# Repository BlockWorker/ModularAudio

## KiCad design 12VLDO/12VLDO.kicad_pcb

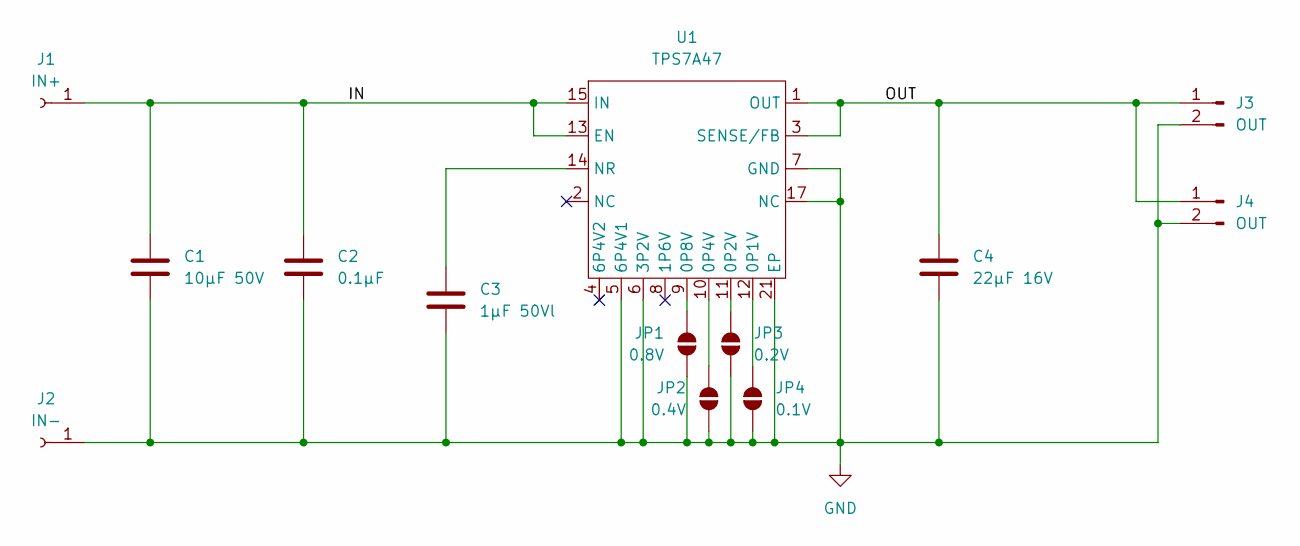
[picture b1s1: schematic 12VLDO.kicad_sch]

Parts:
C1: 10µF 50V; C_1206_3216Metric
C2: 0.1µF; C_0603_1608Metric
C3: 1µF 50Vl; C_0805_2012Metric
C4: 22µF 16V; C_1210_3225Metric
J1: IN+; SolderWirePad_1x01_SMD_1x2mm
J2: IN-; SolderWirePad_1x01_SMD_1x2mm
J3, J4: OUT; Amphenol_MINITEK_0.8_2P_V
JP1: 0.8V; SolderJumper-2_P1.3mm_Open_RoundedPad1.0x1.5mm
JP2: 0.4V; SolderJumper-2_P1.3mm_Open_RoundedPad1.0x1.5mm
JP3: 0.2V; SolderJumper-2_P1.3mm_Open_RoundedPad1.0x1.5mm
JP4: 0.1V; SolderJumper-2_P1.3mm_Open_RoundedPad1.0x1.5mm
U1: TPS7A47; Texas_RGW0020A_VQFN-20-1EP_5x5mm_P0.65mm_EP3.15x3.15mm

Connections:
/IN: C1.1, C2.1, J1.1, U1.13 (EN), U1.15 (IN), U1.16 (IN)
/OUT: C4.1, J3.1, J4.1, U1.1 (OUT), U1.3 (SENSE/FB), U1.20 (OUT)
GND: C1.2, C2.2, C3.2, C4.2, J2.1, J3.2, J4.2, JP1.1 (A), JP2.1 (A), JP3.1 (A), JP4.1 (A), U1.5 (6P4V1), U1.6 (3P2V), U1.7 (GND), U1.17 (NC), U1.18 (NC), U1.19 (NC), U1.21 (EP)
unnamed: JP1.2 (B), U1.9 (0P8V)
unnamed: JP2.2 (B), U1.10 (0P4V)
unnamed: JP3.2 (B), U1.11 (0P2V)
unnamed: JP4.2 (B), U1.12 (0P1V)
unnamed: C3.1, U1.14 (NR)

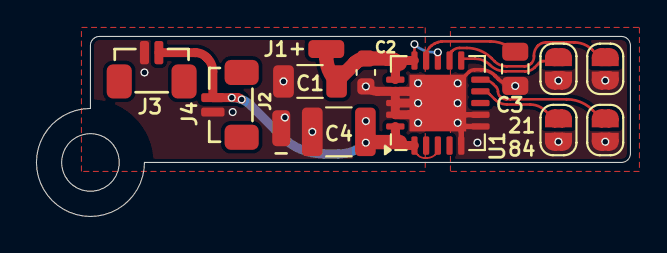
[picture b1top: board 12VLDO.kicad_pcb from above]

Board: 2 copper layers, 33.0 x 10.0 mm, 13 parts (0 on the bottom side), 8 nets.

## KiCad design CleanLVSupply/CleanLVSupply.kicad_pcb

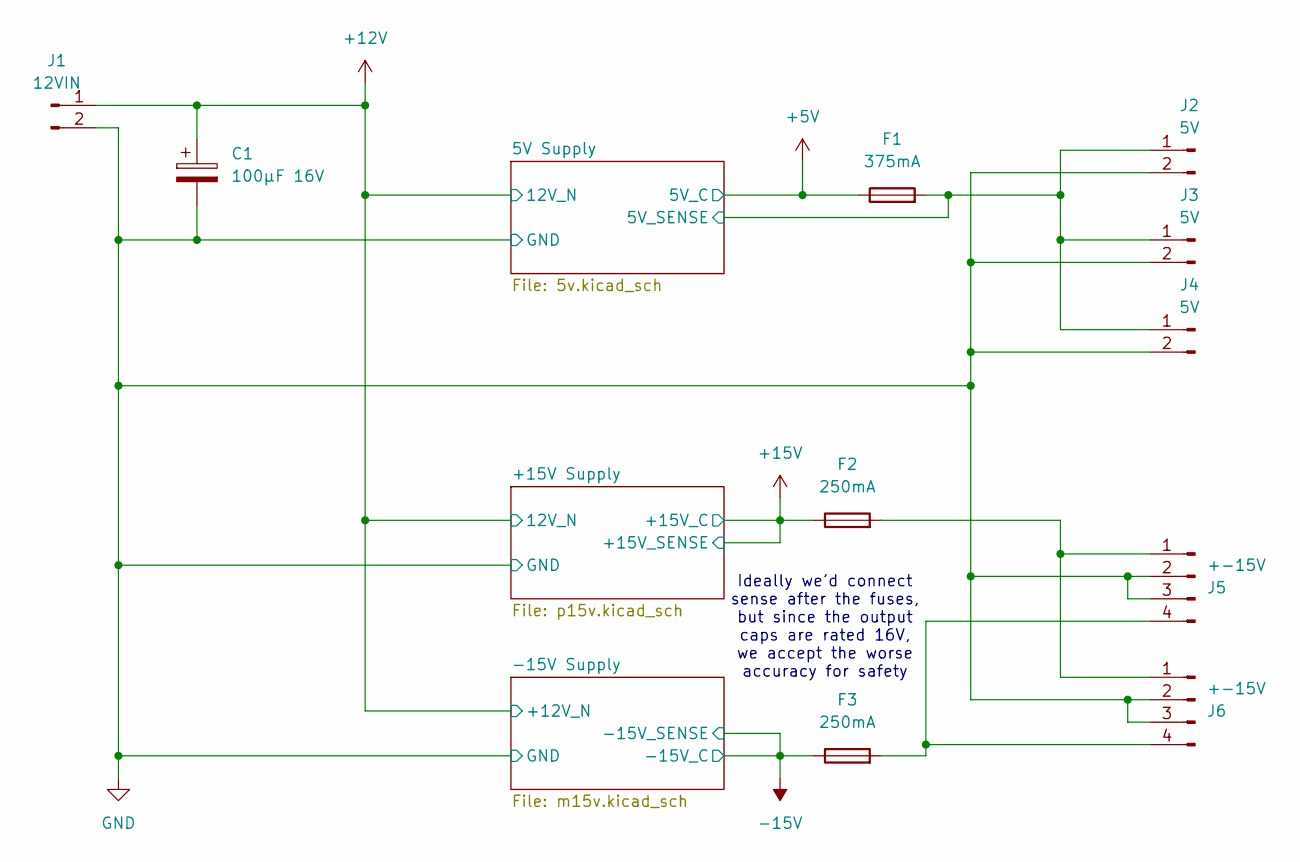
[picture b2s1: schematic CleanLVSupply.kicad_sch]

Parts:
C1: 100µF 16V; CP_Elec_6.3x5.8
F1: 375mA; Fuse_0603_1608Metric
F2, F3: 250mA; Fuse_0603_1608Metric
J1: 12VIN; Amphenol_MINITEK_0.8_2P_V
J2, J3, J4: 5V; Amphenol_MINITEK_0.8_2P_V
J5, J6: +-15V; Amphenol_MINITEK_0.8_4P_V

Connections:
+5V: F1.1; also elsewhere on the board
+12V: C1.1, J1.1; also elsewhere on the board
+15V: F2.1; also elsewhere on the board
-15V: F3.1; also elsewhere on the board
/5V Supply/5V_SENSE: F1.2, J2.1, J3.1, J4.1; also elsewhere on the board
GND: C1.2, J1.2, J2.2, J3.2, J4.2, J5.2, J5.3, J6.2, J6.3; also elsewhere on the board
unnamed: F2.2, J5.1, J6.1
unnamed: F3.2, J5.4, J6.4

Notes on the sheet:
Ideally we'd connect sense after the fuses, but since the output caps are rated 16V, we accept the worse accuracy for safety

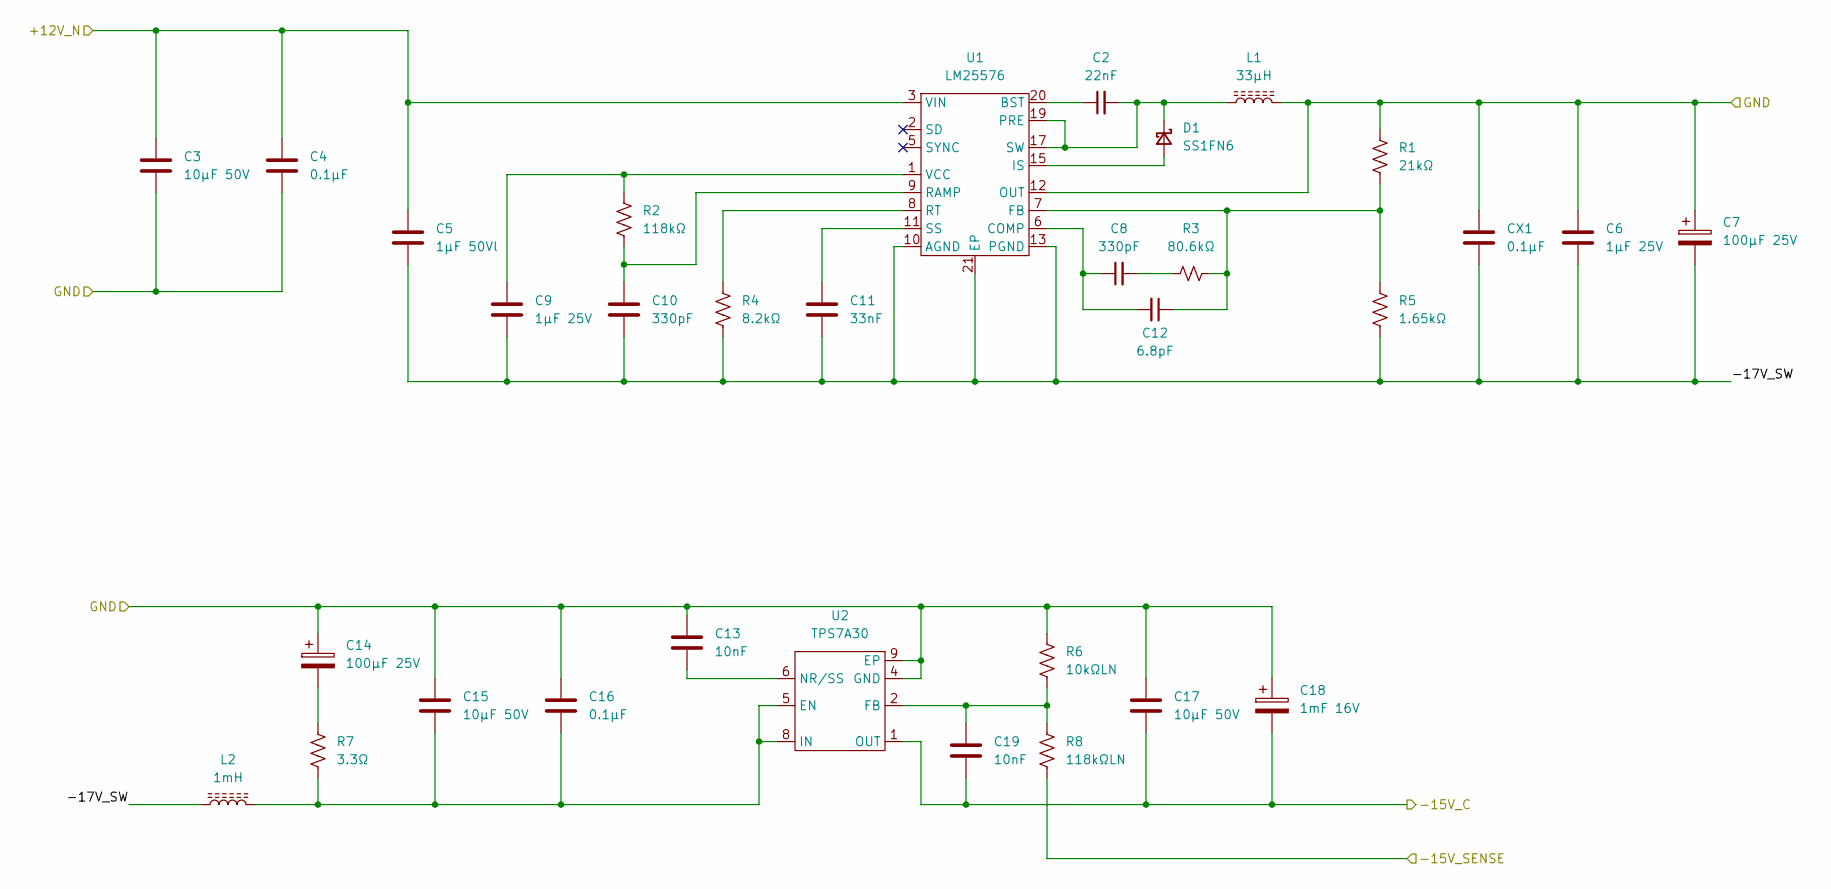
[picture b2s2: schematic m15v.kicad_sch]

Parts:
C2: 22nF; C_0603_1608Metric
C3, C15, C17: 10µF 50V; C_1206_3216Metric
C4, C16: 0.1µF; C_0603_1608Metric
C5: 1µF 50Vl; C_0805_2012Metric
C6, C9: 1µF 25V; C_0603_1608Metric
C7: 100µF 25V; CP_Elec_6.3x7.7
C8, C10: 330pF; C_0603_1608Metric
C11: 33nF; C_0603_1608Metric
C12: 6.8pF; C_0603_1608Metric
C13, C19: 10nF; C_0603_1608Metric
C14: 100µF 25V; CP_Radial_D6.3mm_P2.50mm
C18: 1mF 16V; CP_Radial_D8.0mm_P3.50mm
CX1: 0.1µF; C_0603_1608Metric
D1: SS1FN6; D_SMF
L1: 33µH; L_KEMET_MPGV1D1054
L2: 1mH; L_Coilcraft_MSS7348-XXX-fixed
R1: 21kΩ; R_0603_1608Metric
R2: 118kΩ; R_0603_1608Metric
R3: 80.6kΩ; R_0603_1608Metric
R4: 8.2kΩ; R_0603_1608Metric
R5: 1.65kΩ; R_0603_1608Metric
R6: 10kΩLN; R_0603_1608Metric
R7: 3.3Ω; R_0805_2012Metric
R8: 118kΩLN; R_0603_1608Metric
U1: LM25576; HTSSOP-20-1EP_4.4x6.5mm_P0.65mm_EP2.85x4mm
U2: TPS7A30; HVSSOP-8-1EP_3x3mm_P0.65mm_EP1.57x1.89mm

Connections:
+12V: C3.1, C4.1, C5.1, U1.3 (VIN), U1.4 (VIN); also elsewhere on the board
-15V: C17.2, C18.2, C19.2, R8.2, U2.1 (OUT); also elsewhere on the board
/-15V Supply/-17V_SW: C5.2, C6.2, C7.2, C9.2, C10.2, C11.2, CX1.2, L2.1, R4.2, R5.2, U1.10 (AGND), U1.13 (PGND), U1.14 (PGND), U1.21 (EP)
GND: C3.2, C4.2, C6.1, C7.1, C13.1, C14.1, C15.1, C16.1, C17.1, C18.1, CX1.1, L1.2, R1.1, R6.1, U1.12 (OUT), U2.4 (GND), U2.9 (EP); also elsewhere on the board
unnamed: C8.2, R3.1
unnamed: C14.2, R7.1
unnamed: D1.2 (A), U1.15 (IS), U1.16 (IS)
unnamed: C2.2, D1.1 (K), L1.1, U1.17 (SW), U1.18 (SW), U1.19 (PRE)
unnamed: C2.1, U1.20 (BST)
unnamed: C8.1, C12.2, U1.6 (COMP)
unnamed: C12.1, R1.2, R3.2, R5.1, U1.7 (FB)
unnamed: C10.1, R2.2, U1.9 (RAMP)
unnamed: R4.1, U1.8 (RT)
unnamed: C11.1, U1.11 (SS)
unnamed: C9.1, R2.1, U1.1 (VCC)
unnamed: C15.2, C16.2, L2.2, R7.2, U2.5 (EN), U2.8 (IN)
unnamed: C19.1, R6.2, R8.1, U2.2 (FB)
unnamed: C13.2, U2.6 (NR/SS)

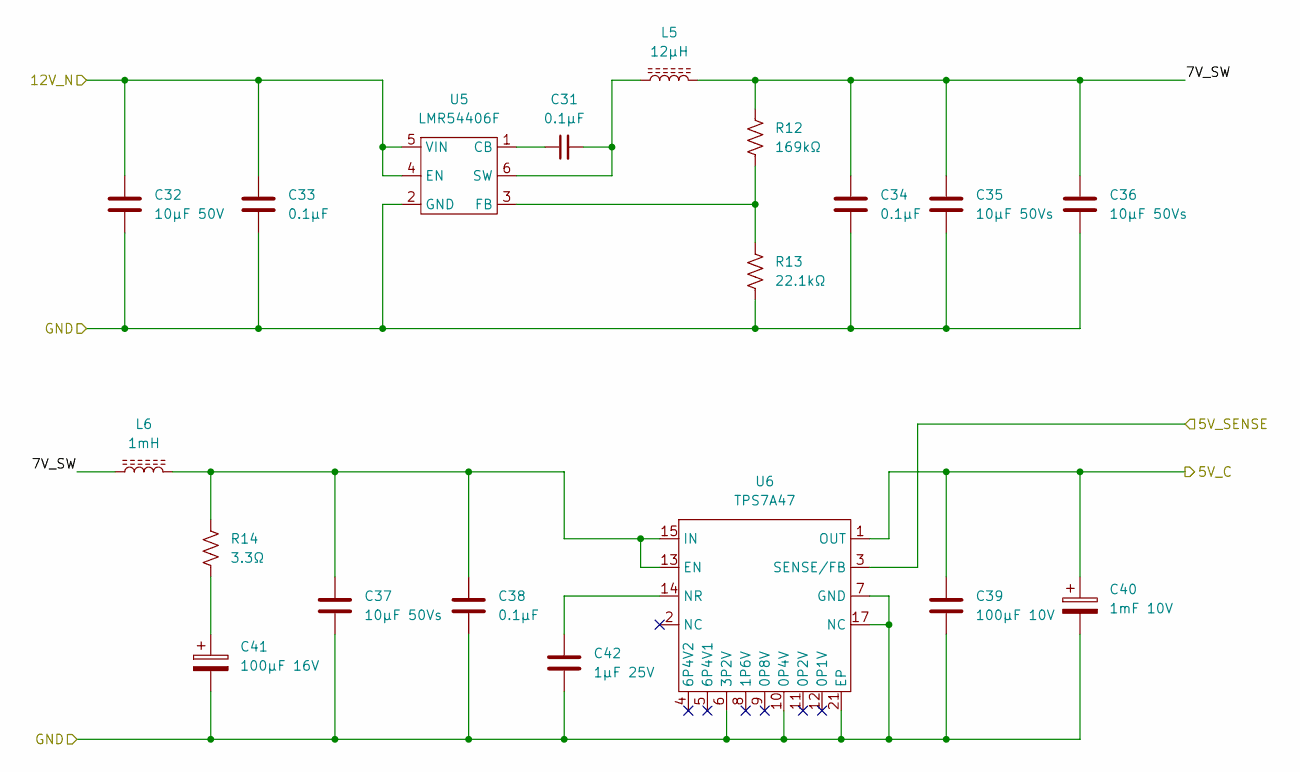
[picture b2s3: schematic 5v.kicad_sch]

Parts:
C31, C33, C34, C38: 0.1µF; C_0603_1608Metric
C32: 10µF 50V; C_1206_3216Metric
C35, C36, C37: 10µF 50Vs; C_0805_2012Metric
C39: 100µF 10V; C_1210_3225Metric
C40: 1mF 10V; CP_Radial_D8.0mm_P3.50mm
C41: 100µF 16V; CP_Radial_D5.0mm_P2.00mm
C42: 1µF 25V; C_0603_1608Metric
L5: 12µH; L_Bourns_SRR4528A
L6: 1mH; L_Coilcraft_MSS7348-XXX-fixed
R12: 169kΩ; R_0603_1608Metric
R13: 22.1kΩ; R_0603_1608Metric
R14: 3.3Ω; R_0805_2012Metric
U5: LMR54406F; SOT-23-6
U6: TPS7A47; Texas_RGW0020A_VQFN-20-1EP_5x5mm_P0.65mm_EP3.15x3.15mm

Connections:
+5V: C39.1, C40.1, U6.1 (OUT), U6.20 (OUT); also elsewhere on the board
+12V: C32.1, C33.1, U5.4 (EN), U5.5 (VIN); also elsewhere on the board
/5V Supply/5V_SENSE: U6.3 (SENSE/FB); also elsewhere on the board
/5V Supply/7V_SW: C34.1, C35.1, C36.1, L5.2, L6.1, R12.1
GND: C32.2, C33.2, C34.2, C35.2, C36.2, C37.2, C38.2, C39.2, C40.2, C41.2, C42.2, R13.2, U5.2 (GND), U6.6 (3P2V), U6.7 (GND), U6.10 (0P4V), U6.17 (NC), U6.18 (NC), U6.19 (NC), U6.21 (EP); also elsewhere on the board
unnamed: C41.1, R14.2
unnamed: C31.1, U5.1 (CB)
unnamed: R12.2, R13.1, U5.3 (FB)
unnamed: C31.2, L5.1, U5.6 (SW)
unnamed: C37.1, C38.1, L6.2, R14.1, U6.13 (EN), U6.15 (IN), U6.16 (IN)
unnamed: C42.1, U6.14 (NR)

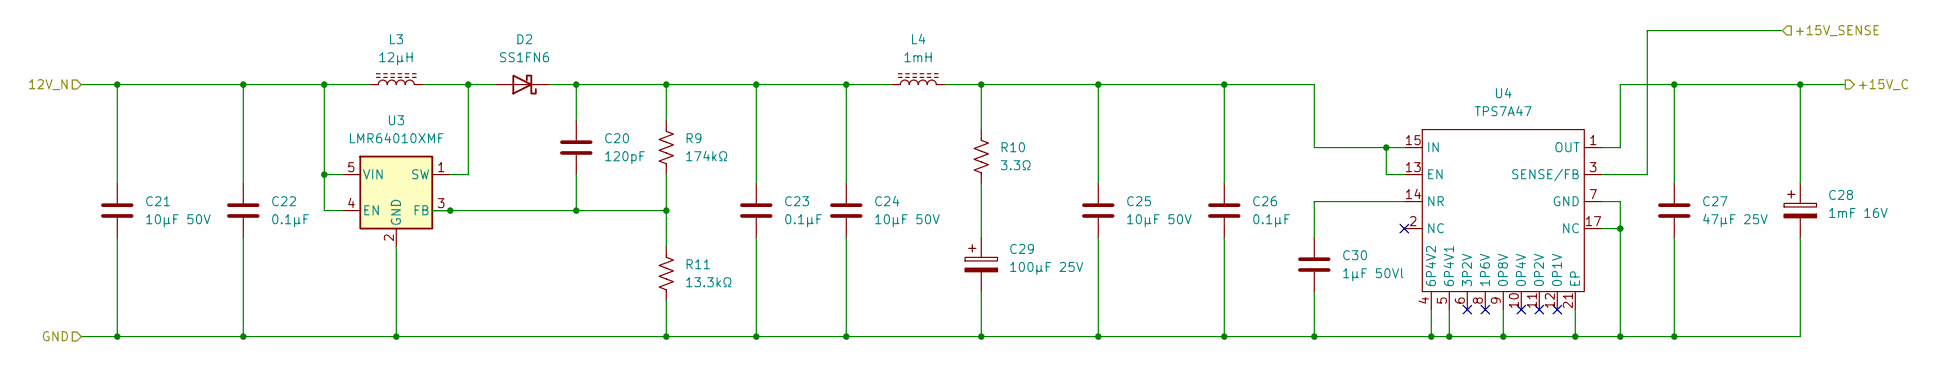
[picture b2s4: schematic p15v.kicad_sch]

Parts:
C20: 120pF; C_0603_1608Metric
C21, C24, C25: 10µF 50V; C_1206_3216Metric
C22, C23, C26: 0.1µF; C_0603_1608Metric
C27: 47µF 25V; C_2220_5750Metric
C28: 1mF 16V; CP_Radial_D8.0mm_P3.50mm
C29: 100µF 25V; CP_Radial_D6.3mm_P2.50mm
C30: 1µF 50Vl; C_0805_2012Metric
D2: SS1FN6; D_SMF
L3: 12µH; L_Abracon_ASPI-6045S
L4: 1mH; L_Coilcraft_MSS7348-XXX-fixed
R9: 174kΩ; R_0603_1608Metric
R10: 3.3Ω; R_0805_2012Metric
R11: 13.3kΩ; R_0603_1608Metric
U3: LMR64010XMF; SOT-23-5
U4: TPS7A47; Texas_RGW0020A_VQFN-20-1EP_5x5mm_P0.65mm_EP3.15x3.15mm

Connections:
+12V: C21.1, C22.1, L3.1, U3.4 (EN), U3.5 (VIN); also elsewhere on the board
+15V: C27.1, C28.1, U4.1 (OUT), U4.3 (SENSE/FB), U4.20 (OUT); also elsewhere on the board
GND: C21.2, C22.2, C23.2, C24.2, C25.2, C26.2, C27.2, C28.2, C29.2, C30.2, R11.2, U3.2 (GND), U4.4 (6P4V2), U4.5 (6P4V1), U4.7 (GND), U4.9 (0P8V), U4.17 (NC), U4.18 (NC), U4.19 (NC), U4.21 (EP); also elsewhere on the board
unnamed: C29.1, R10.2
unnamed: D2.2 (A), L3.2, U3.1 (SW)
unnamed: C20.1, C23.1, C24.1, D2.1 (K), L4.1, R9.1
unnamed: C20.2, R9.2, R11.1, U3.3 (FB)
unnamed: C25.1, C26.1, L4.2, R10.1, U4.13 (EN), U4.15 (IN), U4.16 (IN)
unnamed: C30.1, U4.14 (NR)

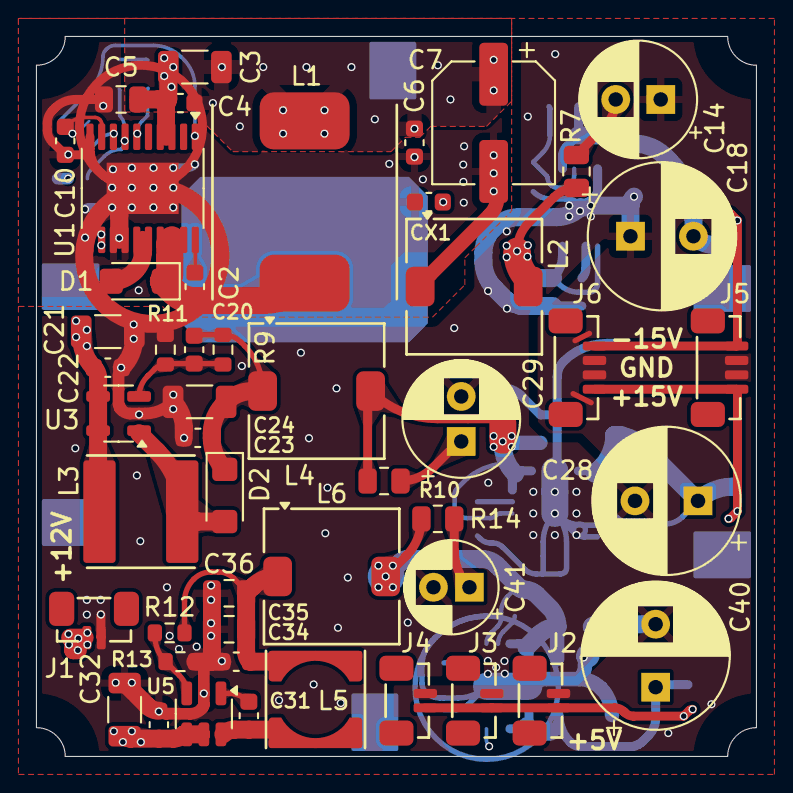
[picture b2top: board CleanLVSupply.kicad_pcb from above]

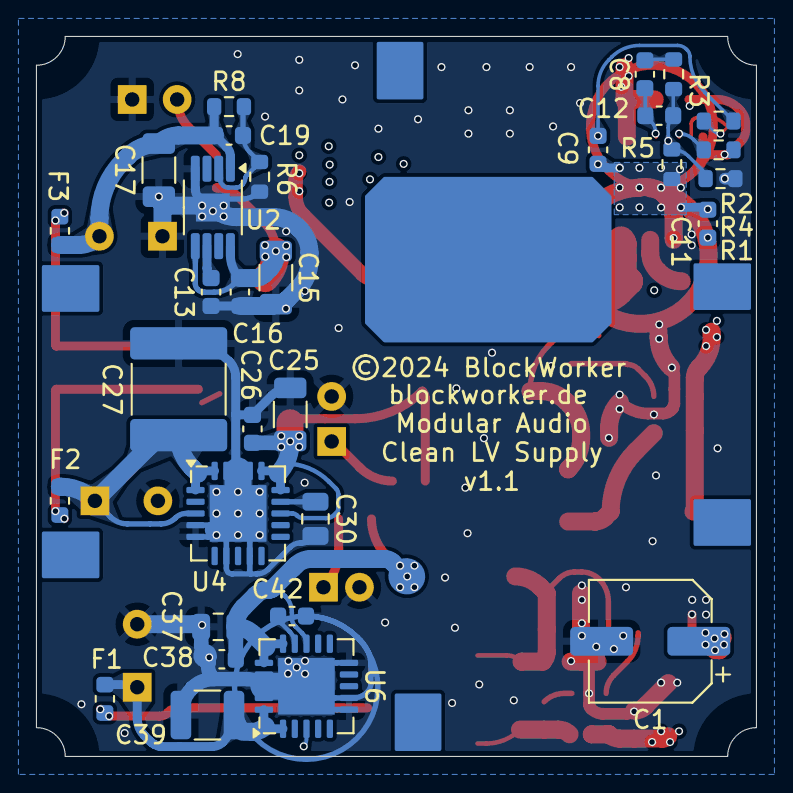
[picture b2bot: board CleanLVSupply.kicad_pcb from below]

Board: 4 copper layers, 40.0 x 40.0 mm, 80 parts (31 on the bottom side), 36 nets.

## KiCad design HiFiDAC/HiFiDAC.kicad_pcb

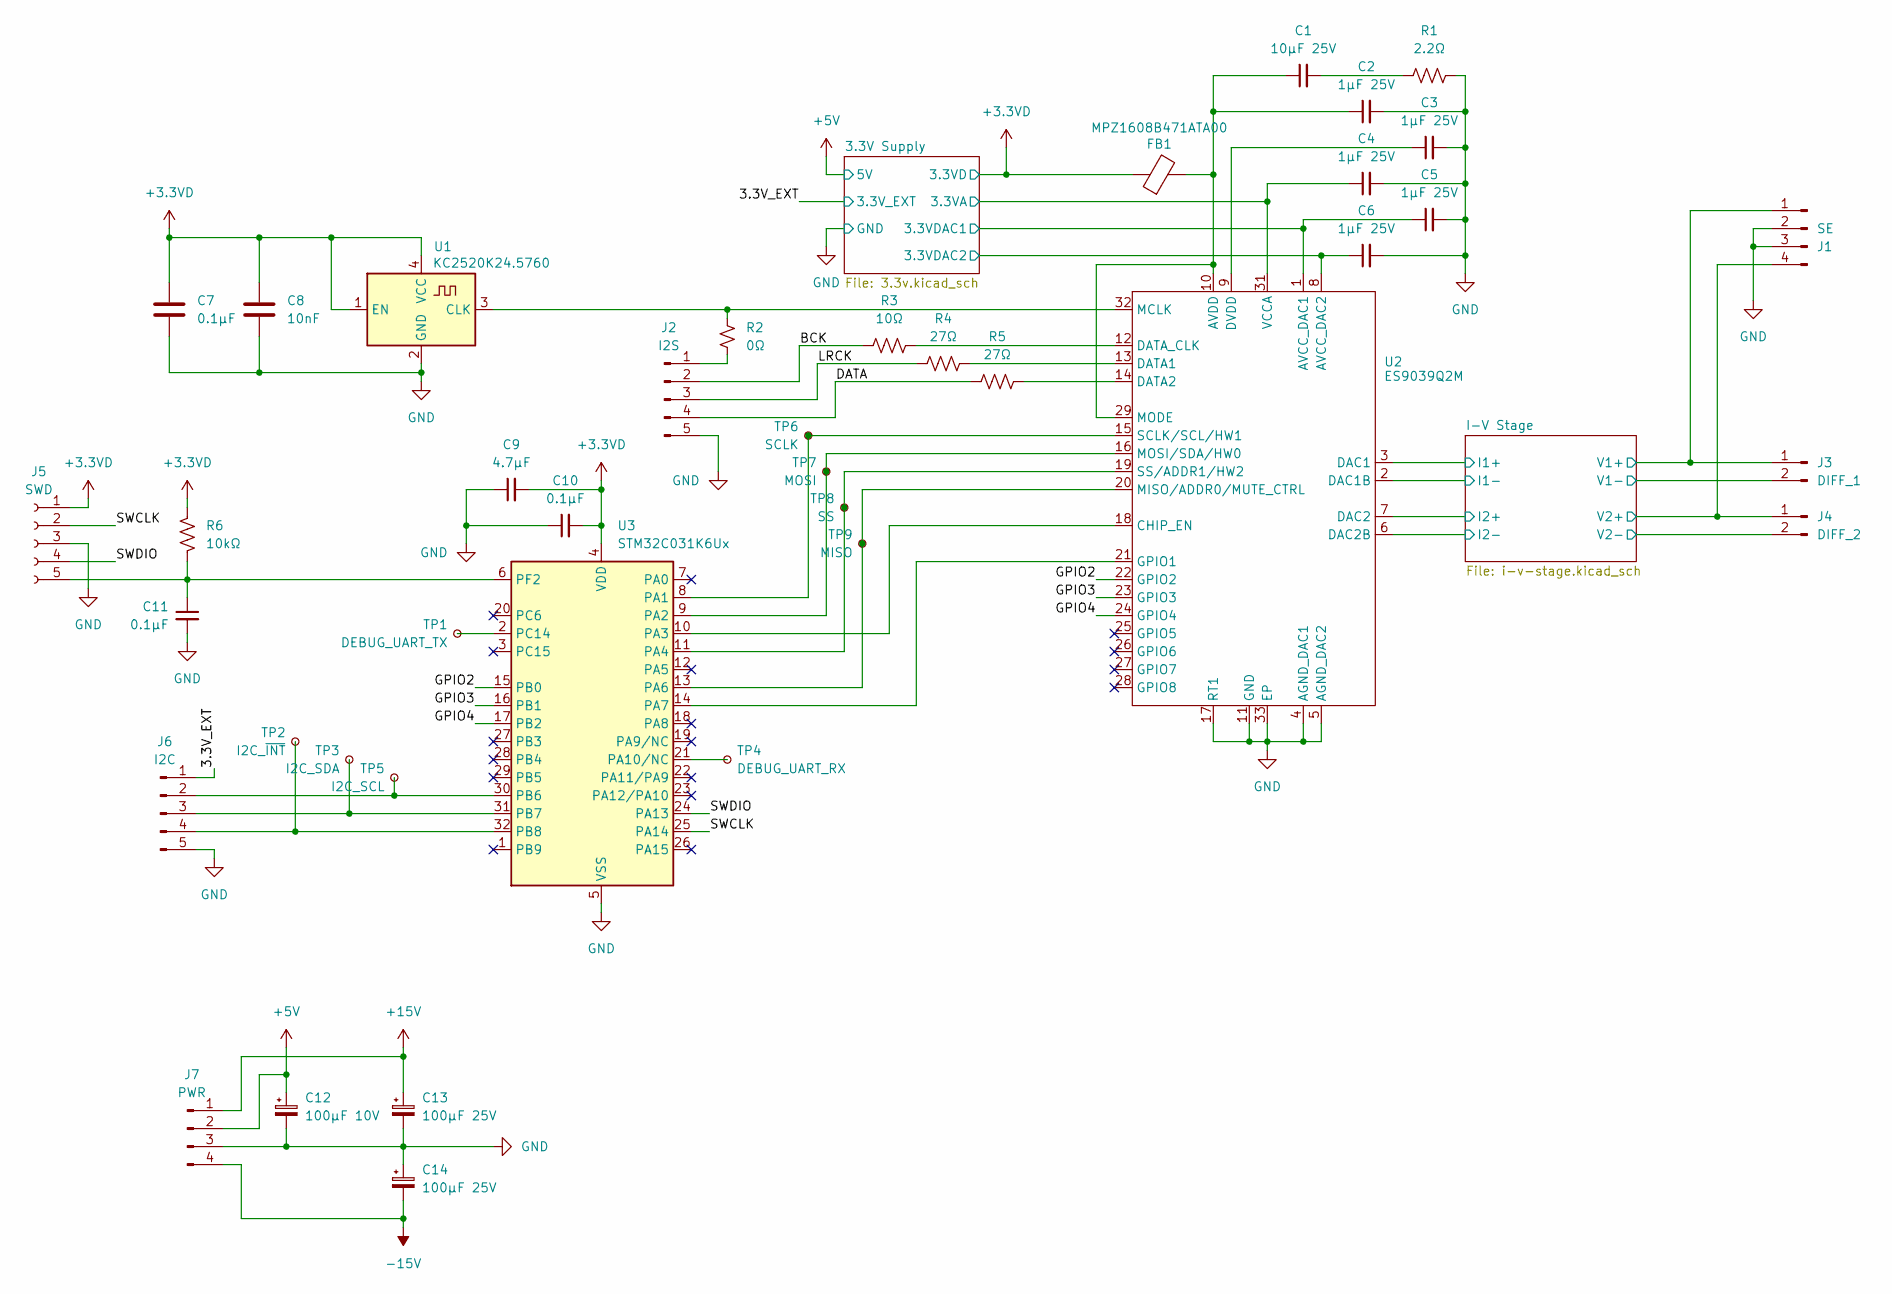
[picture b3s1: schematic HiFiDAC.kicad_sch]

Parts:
C1: 10µF 25V; C_0805_2012Metric
C2, C3, C4, C5, C6: 1µF 25V; C_0603_1608Metric
C7, C10, C11: 0.1µF; C_0603_1608Metric
C8: 10nF; C_0603_1608Metric
C9: 4.7µF; C_0603_1608Metric
C12: 100µF 10V; CP_Radial_D6.3mm_P2.50mm
C13, C14: 100µF 25V; CP_Elec_6.3x5.9
FB1: MPZ1608B471ATA00; L_0603_1608Metric
J1: SE; Amphenol_MINITEK_0.8_4P_V
J2: I2S; Amphenol_MINITEK_WTB_1.25_5P_V
J3: DIFF_1; Amphenol_MINITEK_0.8_2P_V
J4: DIFF_2; Amphenol_MINITEK_0.8_2P_V
J5: SWD; PinSocket_1x05_P1.27mm_Vertical_SMD_Pin1Right
J6: I2C; Amphenol_MINITEK_WTB_1.25_5P_V
J7: PWR; Amphenol_MINITEK_WTB_1.25_4P_V
R1: 2.2Ω; R_0603_1608Metric
R2: 0Ω; R_0603_1608Metric
R3: 10Ω; R_0603_1608Metric
R4, R5: 27Ω; R_0603_1608Metric
R6: 10kΩ; R_0603_1608Metric
TP1: DEBUG_UART_TX; TP_0603_1608Metric_Fused
TP2: I2C_~{INT}; TP_0603_1608Metric_Fused
TP3: I2C_SDA; TP_0603_1608Metric_Fused
TP4: DEBUG_UART_RX; TP_0603_1608Metric_Fused
TP5: I2C_SCL; TP_0603_1608Metric_Fused
TP6: SCLK; TP_0603_1608Metric_Fused
TP7: MOSI; TP_0603_1608Metric_Fused
TP8: SS; TP_0603_1608Metric_Fused
TP9: MISO; TP_0603_1608Metric_Fused
U1: KC2520K24.5760; Oscillator_SMD_Kyocera_KC2520Z-4Pin_2.5x2.0mm
U2: ES9039Q2M; QFN-32-1EP_5x5mm_P0.5mm_EP3.2x3.2mm
U3: STM32C031K6Ux; QFN-32-1EP_5x5mm_P0.5mm_EP3.45x3.45mm

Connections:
+3.3VD: C7.1, C8.1, C9.2, C10.2, FB1.1, J5.1, R6.1, U1.1 (EN), U1.4 (VCC), U3.4 (VDD); also elsewhere on the board
+5V: C12.1, J7.2; also elsewhere on the board
+15V: C13.1, J7.1; also elsewhere on the board
-15V: C14.2, J7.4; also elsewhere on the board
/3.3V Supply/3.3VA: C4.1, U2.31 (VCCA); also elsewhere on the board
/3.3V Supply/3.3VDAC1: C5.1, U2.1 (AVCC_DAC1); also elsewhere on the board
/3.3V Supply/3.3VDAC2: C6.1, U2.8 (AVCC_DAC2); also elsewhere on the board
/3.3V_EXT: J6.1; also elsewhere on the board
/BCK: J2.2, R3.1
/DATA: J2.4, R5.1
/GPIO2: U2.22 (GPIO2), U3.15 (PB0)
/GPIO3: U2.23 (GPIO3), U3.16 (PB1)
/GPIO4: U2.24 (GPIO4), U3.17 (PB2)
/I-V Stage/I1+: U2.3 (DAC1); also elsewhere on the board
/I-V Stage/I1-: U2.2 (DAC1B); also elsewhere on the board
/I-V Stage/I2+: U2.7 (DAC2); also elsewhere on the board
/I-V Stage/I2-: U2.6 (DAC2B); also elsewhere on the board
/I-V Stage/V1+: J1.1, J3.1; also elsewhere on the board
/I-V Stage/V1-: J3.2; also elsewhere on the board
/I-V Stage/V2+: J1.4, J4.1; also elsewhere on the board
/I-V Stage/V2-: J4.2; also elsewhere on the board
/LRCK: J2.3, R4.1
/SWCLK: J5.2, U3.25 (PA14)
/SWDIO: J5.4, U3.24 (PA13)
GND: C2.2, C3.2, C4.2, C5.2, C6.2, C7.2, C8.2, C9.1, C10.1, C11.2, C12.2, C13.2, C14.1, J1.2, J1.3, J2.5, J5.3, J6.5, J7.3, R1.1, U1.2 (GND), U2.4 (AGND_DAC1), U2.5 (AGND_DAC2), U2.11 (GND), U2.17 (RT1), U2.30 (GND), U2.33 (EP), U3.5 (VSS), U3.33 (VSS); also elsewhere on the board
unnamed: C1.2, R1.2
unnamed: J2.1, R2.1
unnamed: C11.1, J5.5, R6.2, U3.6 (PF2)
unnamed: J6.2, TP5.1, U3.30 (PB6)
unnamed: J6.3, TP3.1, U3.31 (PB7)
unnamed: J6.4, TP2.1, U3.32 (PB8)
unnamed: R2.2, U1.3 (CLK), U2.32 (MCLK)
unnamed: C1.1, C2.1, FB1.2, U2.10 (AVDD), U2.29 (MODE)
unnamed: U2.18 (CHIP_EN), U3.10 (PA3)
unnamed: R4.2, U2.13 (DATA1)
unnamed: R5.2, U2.14 (DATA2)
unnamed: R3.2, U2.12 (DATA_CLK)
unnamed: C3.1, U2.9 (DVDD)
unnamed: U2.21 (GPIO1), U3.14 (PA7)
unnamed: TP9.1, U2.20 (MISO/ADDR0/MUTE_CTRL), U3.13 (PA6)
unnamed: TP7.1, U2.16 (MOSI/SDA/HW0), U3.9 (PA2)
unnamed: TP6.1, U2.15 (SCLK/SCL/HW1), U3.8 (PA1)
unnamed: TP8.1, U2.19 (SS/ADDR1/HW2), U3.11 (PA4)
unnamed: TP4.1, U3.21 (PA10/NC)
unnamed: TP1.1, U3.2 (PC14)

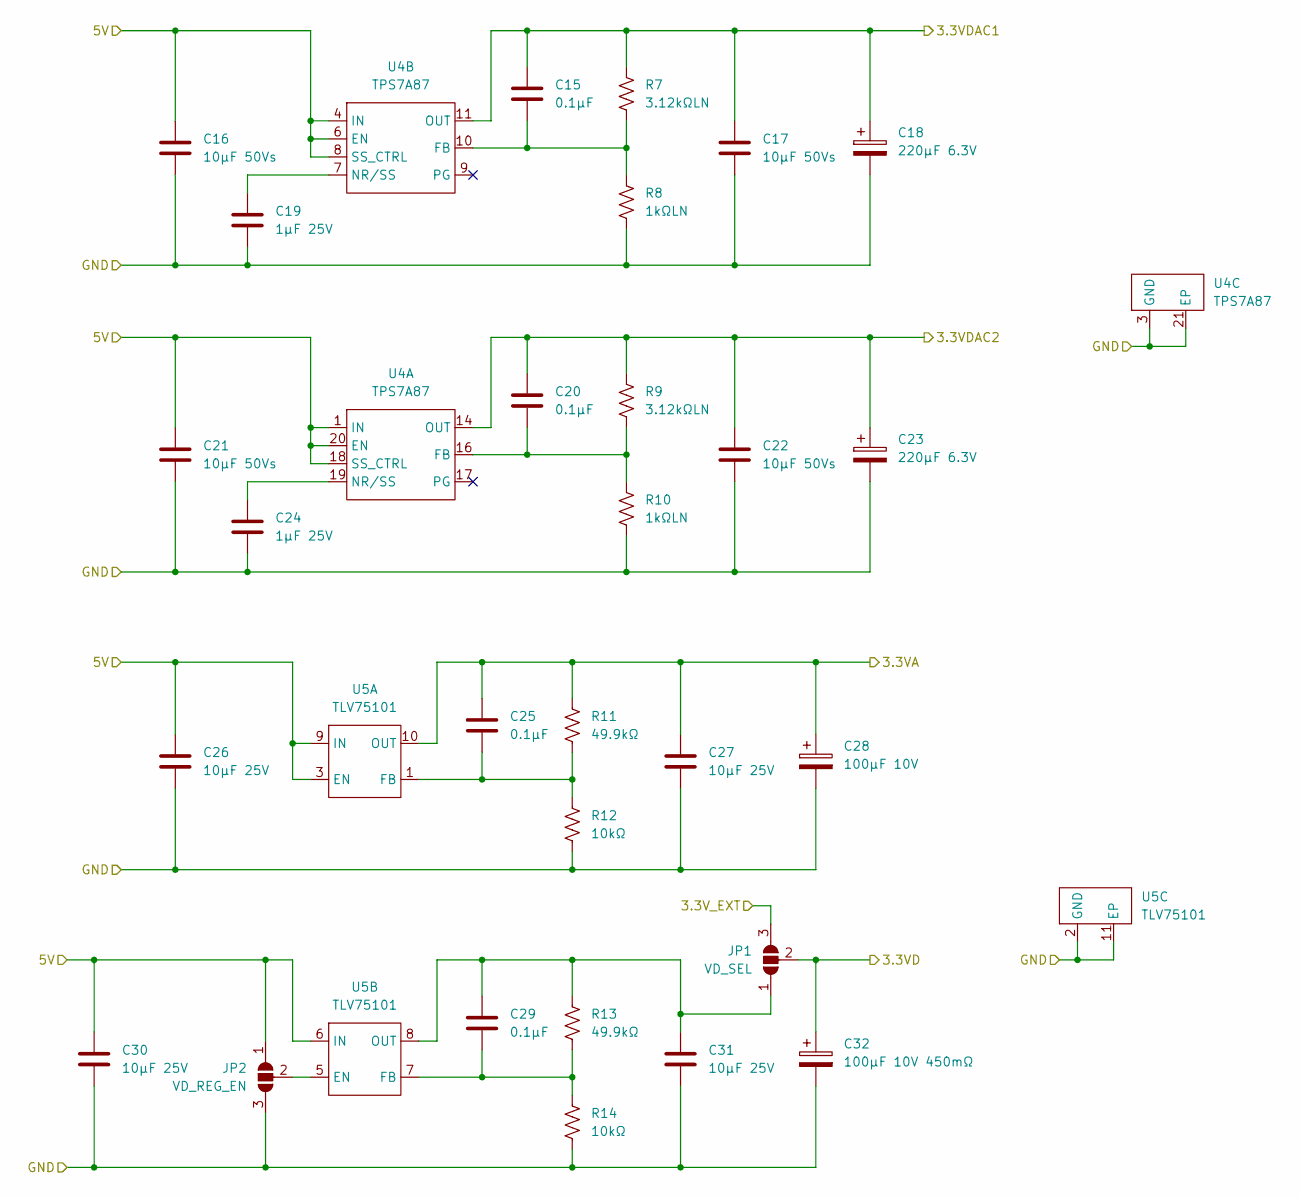
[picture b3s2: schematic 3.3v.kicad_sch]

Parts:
C15, C20, C25, C29: 0.1µF; C_0603_1608Metric
C16, C17, C21, C22: 10µF 50Vs; C_0805_2012Metric
C18, C23: 220µF 6.3V; CP_Radial_D5.0mm_P2.00mm
C19, C24: 1µF 25V; C_0603_1608Metric
C26, C27, C30, C31: 10µF 25V; C_0805_2012Metric
C28: 100µF 10V; CP_Radial_D6.3mm_P2.50mm
C32: 100µF 10V 450mΩ; CP_Elec_6.3x7.7
JP1: VD_SEL; SolderJumper-3_P1.3mm_Open_RoundedPad1.0x1.5mm
JP2: VD_REG_EN; SolderJumper-3_P1.3mm_Open_RoundedPad1.0x1.5mm
R7, R9: 3.12kΩLN; R_0603_1608Metric
R8, R10: 1kΩLN; R_0603_1608Metric
R11, R13: 49.9kΩ; R_0603_1608Metric
R12, R14: 10kΩ; R_0603_1608Metric
U4: TPS7A87; QFN-20-1EP_4x4mm_P0.5mm_EP2.7x2.7mm
U5: TLV75101; WSON-10-1EP_2x2mm_P0.4mm_EP0.9x1.5mm

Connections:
+3.3VD: C32.1, JP1.2 (C); also elsewhere on the board
+5V: C16.1, C21.1, C26.1, C30.1, JP2.1 (A), U4.1 (IN), U4.2 (IN), U4.4 (IN), U4.5 (IN), U4.6 (EN), U4.8 (SS_CTRL), U4.18 (SS_CTRL), U4.20 (EN), U5.3 (EN), U5.6 (IN), U5.9 (IN); also elsewhere on the board
/3.3V Supply/3.3VA: C25.1, C27.1, C28.1, R11.1, U5.10 (OUT); also elsewhere on the board
/3.3V Supply/3.3VDAC1: C15.1, C17.1, C18.1, R7.1, U4.11 (OUT), U4.12 (OUT); also elsewhere on the board
/3.3V Supply/3.3VDAC2: C20.1, C22.1, C23.1, R9.1, U4.14 (OUT), U4.15 (OUT); also elsewhere on the board
/3.3V_EXT: JP1.3 (B); also elsewhere on the board
GND: C16.2, C17.2, C18.2, C19.2, C21.2, C22.2, C23.2, C24.2, C26.2, C27.2, C28.2, C30.2, C31.2, C32.2, JP2.3 (B), R8.2, R10.2, R12.2, R14.2, U4.3 (GND), U4.13 (GND), U4.21 (EP), U5.2 (GND), U5.4 (GND), U5.11 (EP); also elsewhere on the board
unnamed: C29.1, C31.1, JP1.1 (A), R13.1, U5.8 (OUT)
unnamed: JP2.2 (C), U5.5 (EN)
unnamed: C20.2, R9.2, R10.1, U4.16 (FB)
unnamed: C24.1, U4.19 (NR/SS)
unnamed: C15.2, R7.2, R8.1, U4.10 (FB)
unnamed: C19.1, U4.7 (NR/SS)
unnamed: C25.2, R11.2, R12.1, U5.1 (FB)
unnamed: C29.2, R13.2, R14.1, U5.7 (FB)

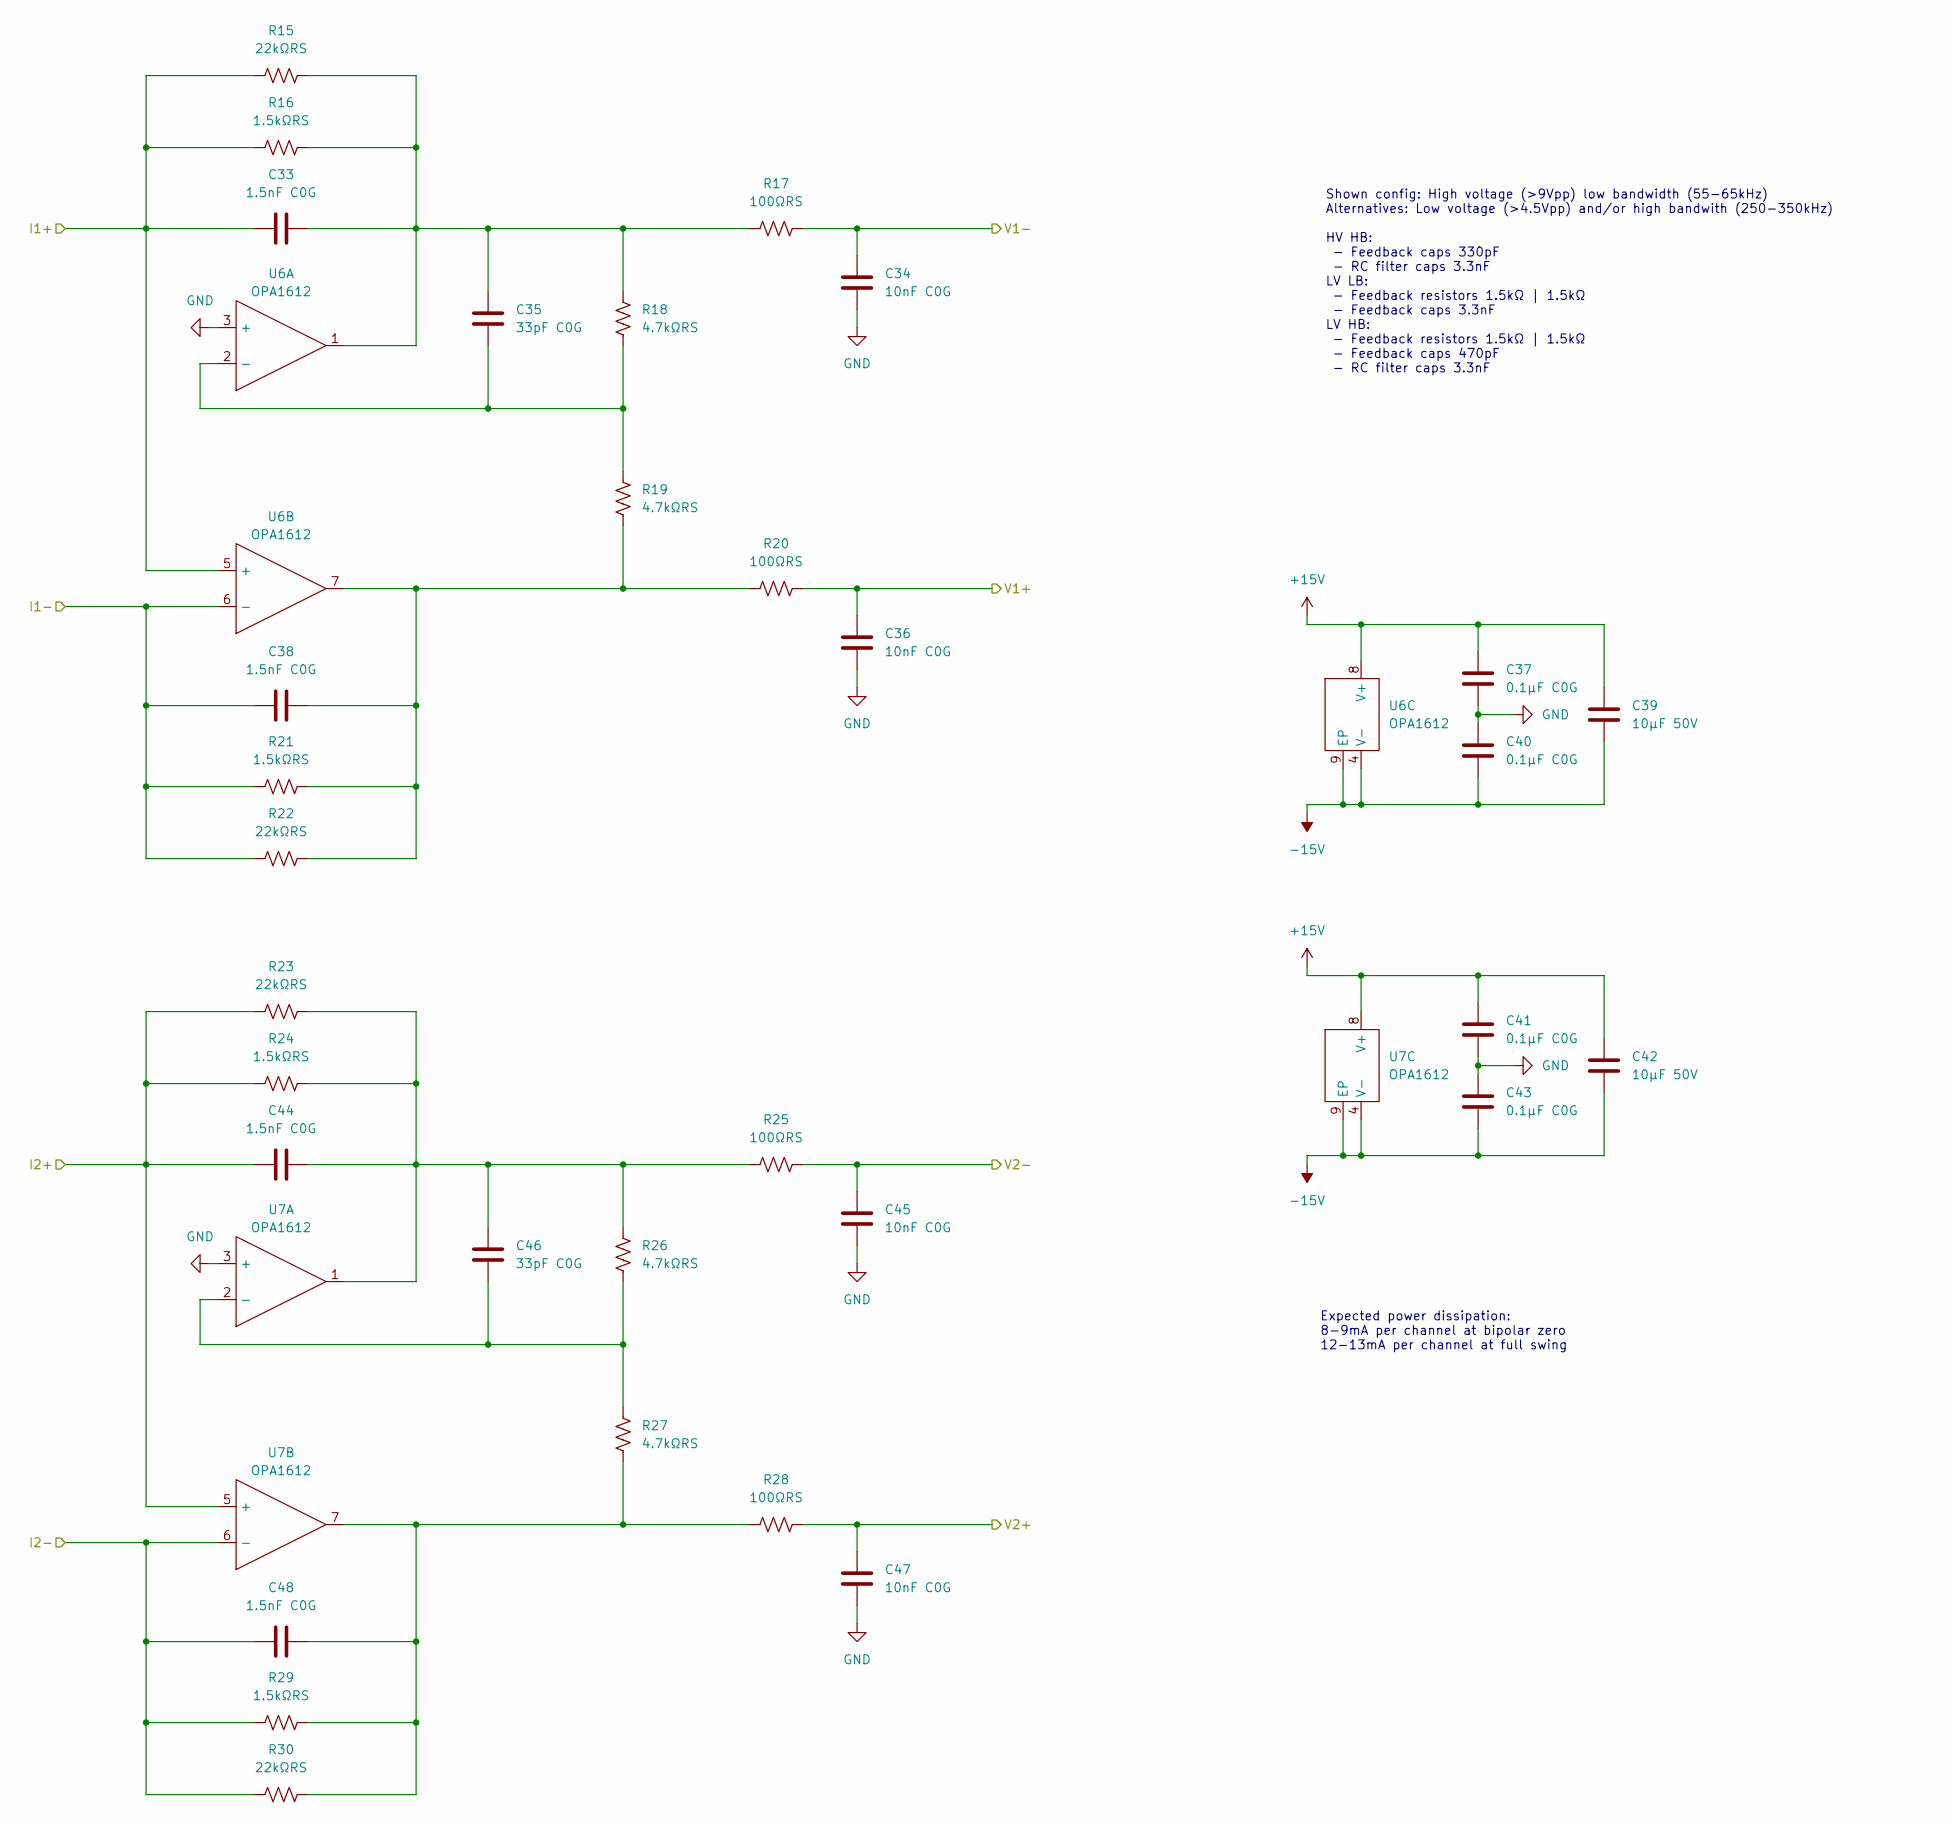
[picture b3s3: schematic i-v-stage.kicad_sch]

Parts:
C33, C38, C44, C48: 1.5nF C0G; C_0603_1608Metric
C34, C36, C45, C47: 10nF C0G; C_0603_1608Metric
C35, C46: 33pF C0G; C_0603_1608Metric
C37, C40, C41, C43: 0.1µF C0G; C_0704_1810Metric
C39, C42: 10µF 50V; C_1206_3216Metric
R15, R22, R23, R30: 22kΩRS; R_0805_2012Metric
R16, R21, R24, R29: 1.5kΩRS; R_0805_2012Metric
R17, R20, R25, R28: 100ΩRS; R_0805_2012Metric
R18, R19, R26, R27: 4.7kΩRS; R_0805_2012Metric
U6, U7: OPA1612; WSON-8-1EP_3x3mm_P0.5mm_EP1.2x2mm

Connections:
+15V: C37.2, C39.1, C41.2, C42.1, U6.8 (V+), U7.8 (V+); also elsewhere on the board
-15V: C39.2, C40.1, C42.2, C43.1, U6.4 (V-), U6.9 (EP), U7.4 (V-), U7.9 (EP); also elsewhere on the board
/I-V Stage/I1+: C33.1, R15.1, R16.1, U6.5 (+); also elsewhere on the board
/I-V Stage/I1-: C38.1, R21.1, R22.1, U6.6 (-); also elsewhere on the board
/I-V Stage/I2+: C44.1, R23.1, R24.1, U7.5 (+); also elsewhere on the board
/I-V Stage/I2-: C48.1, R29.1, R30.1, U7.6 (-); also elsewhere on the board
/I-V Stage/V1+: C36.2, R20.2; also elsewhere on the board
/I-V Stage/V1-: C34.2, R17.2; also elsewhere on the board
/I-V Stage/V2+: C47.2, R28.2; also elsewhere on the board
/I-V Stage/V2-: C45.2, R25.2; also elsewhere on the board
GND: C34.1, C36.1, C37.1, C40.2, C41.1, C43.2, C45.1, C47.1, U6.3 (+), U7.3 (+); also elsewhere on the board
unnamed: C33.2, C35.2, R15.2, R16.2, R17.1, R18.2, U6.1
unnamed: C38.2, R19.1, R20.1, R21.2, R22.2, U6.7
unnamed: C44.2, C46.2, R23.2, R24.2, R25.1, R26.2, U7.1
unnamed: C48.2, R27.1, R28.1, R29.2, R30.2, U7.7
unnamed: C35.1, R18.1, R19.2, U6.2 (-)
unnamed: C46.1, R26.1, R27.2, U7.2 (-)

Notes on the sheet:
Expected power dissipation: 8-9mA per channel at bipolar zero 12-13mA per channel at full swing
Shown config: High voltage (>9Vpp) low bandwidth (55-65kHz) Alternatives: Low voltage (>4.5Vpp) and/or high bandwith (250-350kHz) HV HB: - Feedback caps 330pF - RC filter caps 3.3nF LV LB: - Feedback resistors 1.5kΩ | 1.5kΩ - Feedback caps 3.3nF LV HB: - Feedback resistors 1.5kΩ | 1.5kΩ - Feedback 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

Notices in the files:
parts and their libraries:
©2024 BlockWorker
